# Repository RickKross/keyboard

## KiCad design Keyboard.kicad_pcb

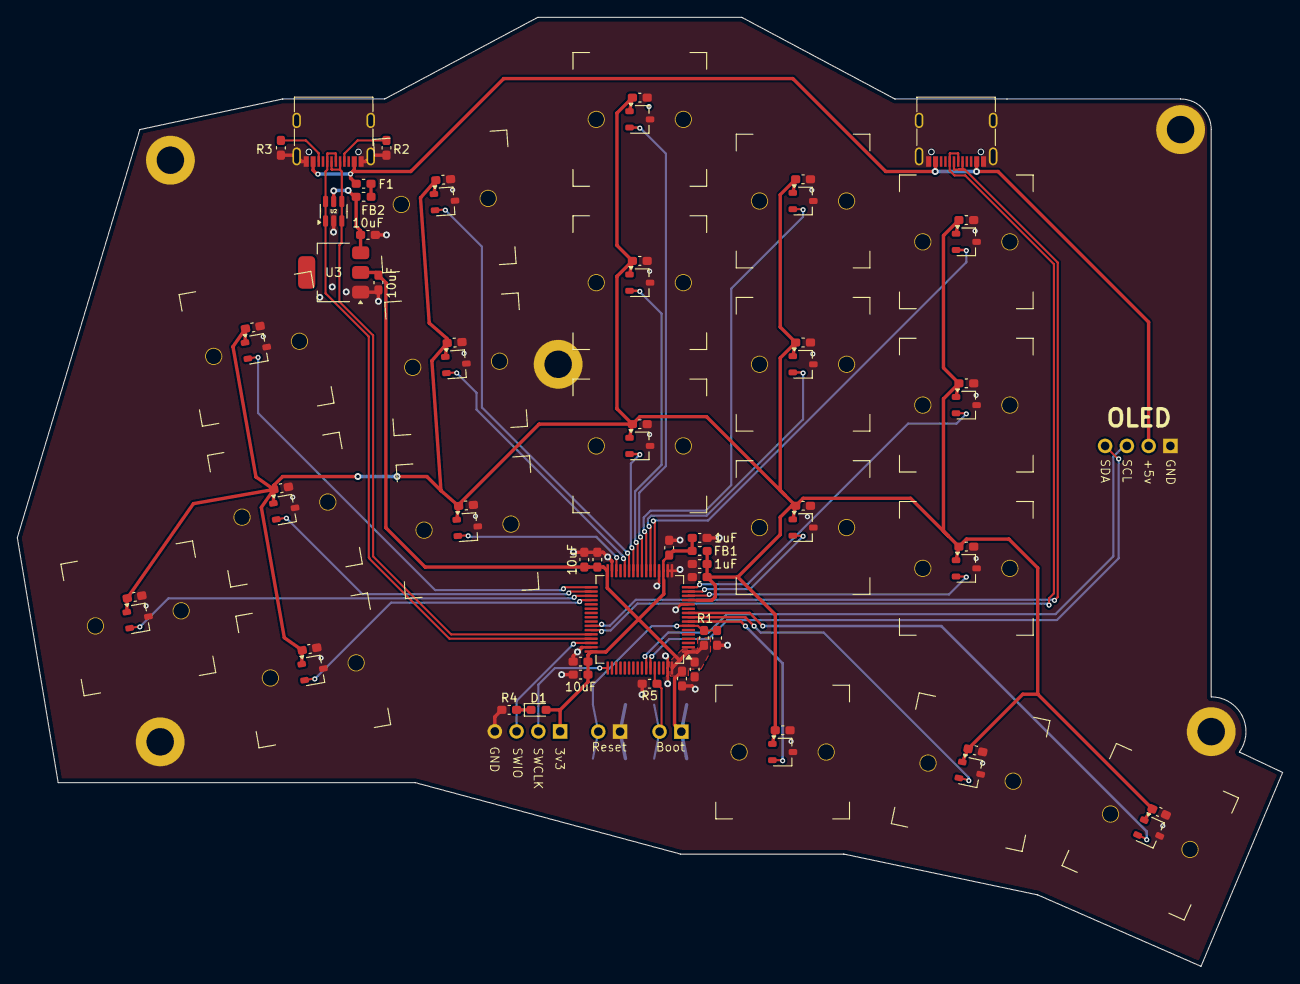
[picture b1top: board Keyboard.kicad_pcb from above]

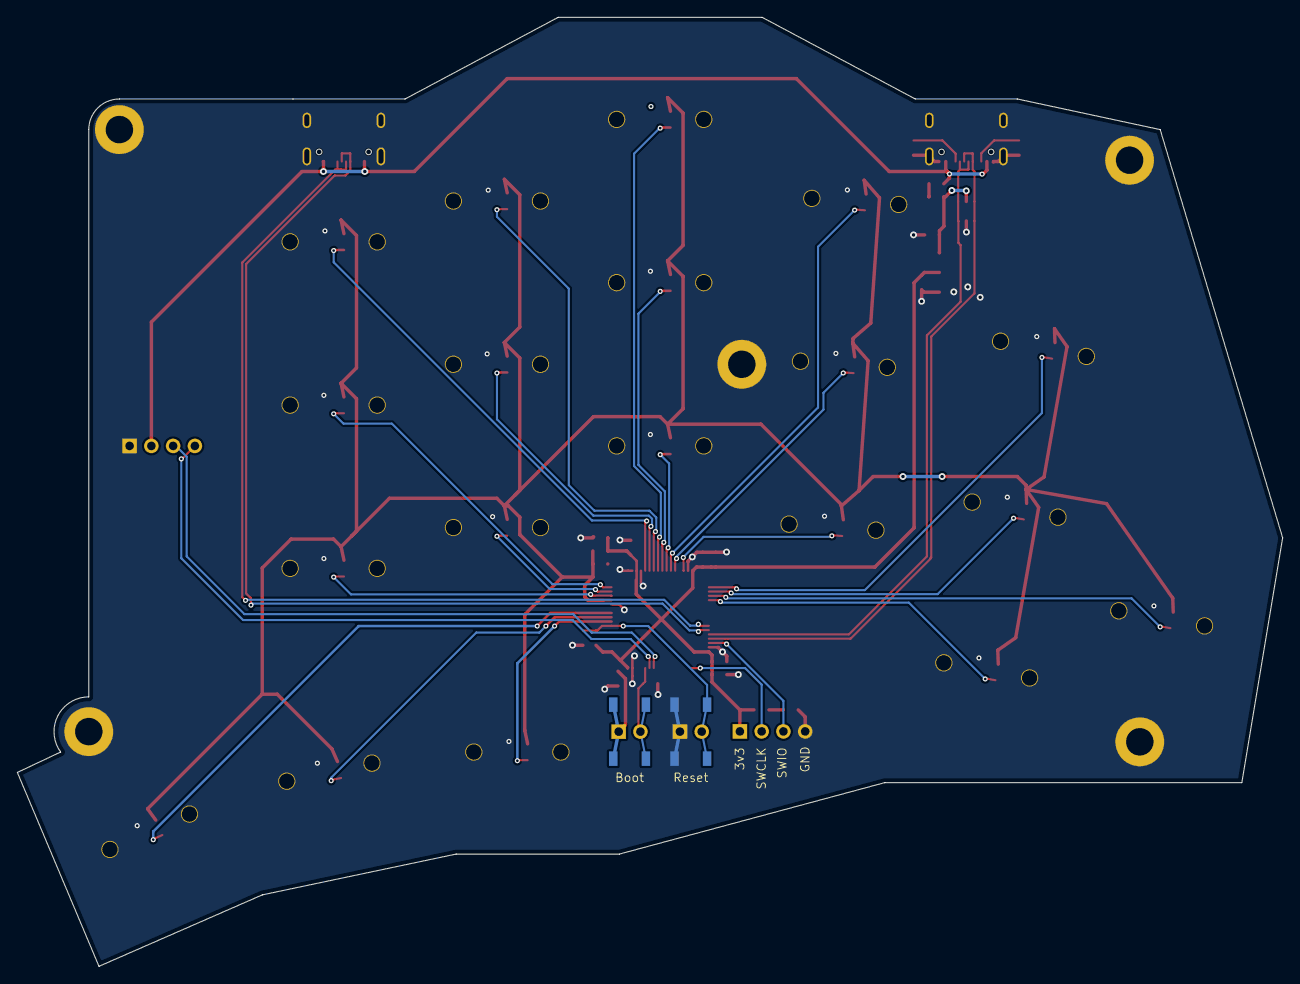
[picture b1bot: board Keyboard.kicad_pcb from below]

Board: 2 copper layers, 147.6 x 110.7 mm, 95 parts (4 on the bottom side), 38 nets.

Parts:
C1, C2, C3, C4, C5, C6, C7, C8, C9, C10, C11, C12, C13, C14, C15, C16, C17, C18, C19, C21, C22, C23, C24, C25, C26, C29: 100nF; C_0603_1608Metric_Pad1.08x0.95mm_HandSolder
C20, C30, C31, C32: 10uF; C_0603_1608Metric_Pad1.08x0.95mm_HandSolder
C27, C28: 1uF; C_0603_1608Metric_Pad1.08x0.95mm_HandSolder
D1: RED; LED_0603_1608Metric_Pad1.05x0.95mm_HandSolder
F1: 600mA; C_0603_1608Metric_Pad1.08x0.95mm_HandSolder
FB1, FB2: BLM18KG121TN1D; L_0603_1608Metric_Pad1.05x0.95mm_HandSolder
H1, H2, H3, H4, H5: MountingHole_Pad; MountingHole_3.2mm_M3_ISO7380_Pad
HS1, HS2, HS3, HS4, HS5, HS6, HS7, HS8, HS9, HS10, HS11, HS12, HS13, HS14, HS15, HS16, HS17, HS18, HS19: GH39FKSW; SOT-23W
J1, J5: PinHeader_1x02_P2.54mm_Vertical
J2: USB_C; USB_C_Receptacle_G-Switch_GT-USB-7010ASV
J3: USB_C_Receptacle_USB2.0_14P; USB_C_Receptacle_G-Switch_GT-USB-7010ASV
J4: Conn_01x04_Pin; PinHeader_1x04_P2.54mm_Vertical
MX1, MX2, MX3, MX4, MX5, MX6, MX7, MX8, MX9, MX10, MX11, MX12, MX13, MX14, MX15, MX16, MX17, MX18, MX19: MX 1.00u
O1: OLED_128x32
R1: 40k; C_0603_1608Metric_Pad1.08x0.95mm_HandSolder
R2, R3, R4: 5.1k; C_0603_1608Metric_Pad1.08x0.95mm_HandSolder
R5: 10k; C_0603_1608Metric_Pad1.08x0.95mm_HandSolder
SW1, SW2: SW_Push; SW_SPST_TL3342
U1: STM32F303RETx; LQFP-64_10x10mm_P0.5mm
U2: USBLC6-2SC6; SOT-23-6
U3: AMS1117-3.3; SOT-223-3_TabPin2

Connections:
+3.3VA: C1.2, C2.2, C3.2, C4.2, C5.2, C6.2, C7.2, C8.2, C9.2, C10.2, C11.2, C12.2, C13.2, C14.2, C15.2, C16.2, C17.2, C18.2, C19.2, C26.1, C27.1, FB1.1, HS1.1 (VCC), HS2.1 (VCC), HS3.1 (VCC), HS4.1 (VCC), HS5.1 (VCC), HS6.1 (VCC), HS7.1 (VCC), HS8.1 (VCC), HS9.1 (VCC), HS10.1 (VCC), HS11.1 (VCC), HS12.1 (VCC), HS13.1 (VCC), HS14.1 (VCC), HS15.1 (VCC), HS16.1 (VCC), HS17.1 (VCC), HS18.1 (VCC), HS19.1 (VCC), U1.13 (VDDA)
+3V3: C20.1, C21.1, C22.1, C23.1, C24.1, C25.1, C28.1, C31.1, C32.2, D1.2 (A), FB1.2, J4.1, J5.1, R1.2, SW2.1, U1.1 (VBAT), U1.19 (VDD), U1.32 (VDD), U1.48 (VDD), U1.64 (VDD), U3.2 (VO)
+5V: C30.1, FB2.2, U2.5 (VBUS), U3.3 (VI)
BOOT: J5.2, R5.2, SW2.2, U1.60 (BOOT0)
D+: J2.A6 (D+), J2.B6 (D+), U1.45 (PA12), U2.1 (I/O1), U2.6 (I/O1)
D-: J2.A7 (D-), J2.B7 (D-), U1.44 (PA11), U2.3 (I/O2), U2.4 (I/O2)
GND: C1.1, C2.1, C3.1, C4.1, C5.1, C6.1, C7.1, C8.1, C9.1, C10.1, C11.1, C12.1, C13.1, C14.1, C15.1, C16.1, C17.1, C18.1, C19.1, C20.2, C21.2, C22.2, C23.2, C24.2, C25.2, C26.2, C27.2, C28.2, C29.1, C30.2, C31.2, C32.1, H1.1, H2.1, H3.1, H4.1, H5.1, HS1.3 (GND), HS2.3 (GND), HS3.3 (GND), HS4.3 (GND), HS5.3 (GND), HS6.3 (GND), HS7.3 (GND), HS8.3 (GND), HS9.3 (GND), HS10.3 (GND), HS11.3 (GND), HS12.3 (GND), HS13.3 (GND), HS14.3 (GND), HS15.3 (GND), HS16.3 (GND), HS17.3 (GND), HS18.3 (GND), HS19.3 (GND), J1.1, J2.A1 (GND), J2.A12 (GND), J2.B1 (GND), J2.B12 (GND), J2.S1 (SHIELD), J3.A1 (GND), J3.A12 (GND), J3.B1 (GND), J3.B12 (GND), J3.S1 (SHIELD), J4.4, MX1.1 (GND), MX2.1 (GND), MX3.1 (GND), MX4.1 (GND), MX5.1 (GND), MX6.1 (GND), MX7.1 (GND), MX8.1 (GND), MX9.1 (GND), MX10.1 (GND), MX11.1 (GND), MX12.1 (GND), MX13.1 (GND), MX14.1 (GND), MX15.1 (GND), MX16.1 (GND), MX17.1 (GND), MX18.1 (GND), MX19.1 (GND), O1.1 (GND), R2.2, R3.2, R4.2, R5.1, SW1.1, U1.12 (VSSA), U1.17 (PA3), U1.18 (VSS), U1.20 (PA4), U1.31 (VSS), U1.47 (VSS), U1.63 (VSS), U2.2 (GND), U3.1 (GND)
L:SW:0:0: HS5.2 (VOUT), U1.21 (PA5)
L:SW:0:1: HS4.2 (VOUT), U1.23 (PA7)
L:SW:0:2: HS3.2 (VOUT), U1.24 (PC4)
L:SW:0:3: HS2.2 (VOUT), U1.27 (PB1)
L:SW:0:4: HS1.2 (VOUT), U1.33 (PB12)
L:SW:1:0: HS11.2 (VOUT), U1.16 (PA2)
L:SW:1:1: HS10.2 (VOUT), U1.22 (PA6)
L:SW:1:2: HS9.2 (VOUT), U1.25 (PC5)
L:SW:1:3: HS8.2 (VOUT), U1.28 (PB2)
L:SW:1:4: HS7.2 (VOUT), U1.34 (PB13)
L:SW:1:5: HS6.2 (VOUT), U1.35 (PB14)
L:SW:2:0: HS16.2 (VOUT), U1.14 (PA0)
L:SW:2:1: HS15.2 (VOUT), U1.15 (PA1)
L:SW:2:2: HS14.2 (VOUT), U1.26 (PB0)
L:SW:2:3: HS13.2 (VOUT), U1.30 (PB11)
L:SW:2:4: HS12.2 (VOUT), U1.36 (PB15)
L:SW:3:0: HS19.2 (VOUT), U1.10 (PC2)
L:SW:3:1: HS18.2 (VOUT), U1.9 (PC1)
L:SW:3:2: HS17.2 (VOUT), U1.8 (PC0)
NRST: C29.2, J1.2, R1.1, SW1.2, U1.7 (NRST)
unnamed: D1.1 (K), R4.1
unnamed: F1.2, FB2.1
unnamed: J2.A5 (CC1), R2.1
unnamed: J2.B5 (CC2), R3.1
RX: J3.A6 (D+), J3.B6 (D+), U1.43 (PA10)
SCL: O1.3 (SCL), U1.58 (PB6)
SDA: O1.4 (SDA), U1.59 (PB7)
SWCLK: J4.2, U1.49 (PA14)
SWIO: J4.3, U1.46 (PA13)
TX: J3.A7 (D-), J3.B7 (D-), U1.42 (PA9)
VBUS: F1.1, J2.A4 (VBUS), J2.A9 (VBUS), J2.B4 (VBUS), J2.B9 (VBUS), J3.A4 (VBUS), J3.A9 (VBUS), J3.B4 (VBUS), J3.B9 (VBUS), O1.2 (VCC)

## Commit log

2024-12-23 Create LICENSE
2024-12-23 left half v0
2024-12-23 ibom v0
2024-12-23 ibom v0 fixes
